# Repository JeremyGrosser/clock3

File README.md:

This repository contains firmware for my 3 time zone clock based on the [Adafruit Feather M0 Wifi](https://www.adafruit.com/product/3010). This project is very incomplete and is unlikely to be reproducible with the code listed here.

Some of the software components (eg. samd21 drivers) may be useful to others, so I'm making this repository public, but have no intention to maintain it long term.

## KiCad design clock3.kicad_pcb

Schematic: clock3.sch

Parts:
BAT1: BS-7; Battery_Holder_Coin_2032_BS-7; MPN BS-7; Digi-Key_PN BS-7-ND
BOOT1, BOOT2: EG1218; Switch_Slide_11.6x4mm_EG1218; MPN EG1218; Digi-Key_PN EG1903-ND
C1, C2, C9: 4.7uF; C_0603_1608Metric
C3: 10uF; C_0805_2012Metric
C4, C5: 16pF; C_0603_1608Metric
C6, C7, C8, C12, C13, C14, C15: 100nF; C_0603_1608Metric
C10: 10nF; C_0603_1608Metric
C11: 1uF; C_0603_1608Metric
C17, C18: 5pF; C_0603_1608Metric
D1, D2, D3, D4: LED; LED_1206_3216Metric
J1: 10118194-0001LF; USB_Micro_B_Female_10118194-0001LF; MPN 10118194-0001LF; Digi-Key_PN 609-4618-1-ND
J2: SWD; Molex_KK-254_AE-6410-06A_1x06_P2.54mm_Vertical
J3, J4, J5: Conn_01x06_Male; Molex_KK-254_AE-6410-06A_1x06_P2.54mm_Vertical
MK1, MK2, MK3, MK4: Mounting_Hole_PAD; MountingHole_2.2mm_M2_DIN965_Pad
R2, R3: 10k; R_0603_1608Metric
R4, R5, R6, R7: R; R_0603_1608Metric
S1, S2, S3, S4: B3F-3150
U1: AP2114H-3_3TRG1; SOT-223; MPN AP2114H-3.3TRG1; Digi-Key_PN AP2114H-3.3TRG1DICT-ND
U2: STM32F102CBTx; LQFP-48_7x7mm_P0.5mm
Y1: 8MHz 18pF 30ppm; Crystal_SMD_HC49-US_AT49
Y2: 32.768kHz 12.5pF 20ppm; Crystal_SMD_SeikoEpson_MC146-4Pin_6.7x1.5mm

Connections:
/BOOT0: R2.2, U2.44 (BOOT0)
/BOOT1: R3.2, U2.20 (PB2)
/BUTTON1: C12.2, S1.1, U2.28 (PB15)
/BUTTON2: C13.2, S2.1, U2.27 (PB14)
/BUTTON3: C14.2, S3.1, U2.26 (PB13)
/I2C1_SCL: J3.4, J4.4, J5.4, U2.42 (PB6)
/I2C1_SDA: J3.3, J4.3, J5.3, U2.43 (PB7)
/LED1: D1.1, U2.10 (PA0)
/LED2: D2.1, U2.11 (PA1)
/LED3: D3.1, U2.29 (PA8)
/SWCLK: J2.2, U2.37 (PA14)
/SWDIO: J2.4, U2.34 (PA13)
/SWO: J2.6, U2.39 (PB3)
/USB_D+: J1.3, U2.33 (PA12)
/USB_D-: J1.2, U2.32 (PA11)
/VBAT: BAT1.Pos, U2.1 (VBAT)
/~RESET: C15.2, J2.5, S4.1, U2.7 (NRST)
GND: BAT1.Neg, BOOT1.3, BOOT2.3, C1.2, C2.2, C3.2, C4.2, C5.2, C6.2, C7.2, C8.2, C9.2, C10.2, C11.2, C12.1, C13.1, C14.1, C15.1, C17.2, C18.2, J1.4, J1.5, J1.SH, J2.3, J3.2, J3.6, J4.2, J4.6, J5.2, J5.6, MK1.1, MK2.1, MK3.1, MK4.1, S1.2, S1.3, S1.4, S2.2, S2.3, S2.4, S3.2, S3.3, S3.4, S4.2, S4.3, S4.4, U1.1, U2.8 (VSSA), U2.23 (VSS), U2.35 (VSS), U2.47 (VSS)
unnamed: BOOT1.2, R2.1
unnamed: BOOT2.2, R3.1
unnamed: C4.1, U2.5 (PD0), Y1.2
unnamed: C5.1, U2.6 (PD1), Y1.1
unnamed: C17.1, U2.3 (PC14), Y2.2
unnamed: C18.1, U2.4 (PC15), Y2.1
unnamed: D1.2, R4.2
unnamed: D2.2, R5.2
unnamed: D3.2, R6.2
unnamed: D4.2, R7.2
VCC: C1.1, J1.1, J3.1, J4.1, J5.1, U1.3
VDD: BOOT1.1, BOOT2.1, C2.1, C3.1, C6.1, C7.1, C8.1, C9.1, C10.1, C11.1, J2.1, J3.5, J4.5, J5.5, R4.1, R5.1, R6.1, R7.1, U1.2, U1.4, U2.9 (VDDA), U2.24 (VDD), U2.36 (VDD), U2.48 (VDD)

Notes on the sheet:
POWER 5V IN 3.3V @ 1A OUT
DEBUG
LED DISPLAYS
USB
BUTTONS AND SWITCHES
WIFI
LEDS
VDD3
VDDA

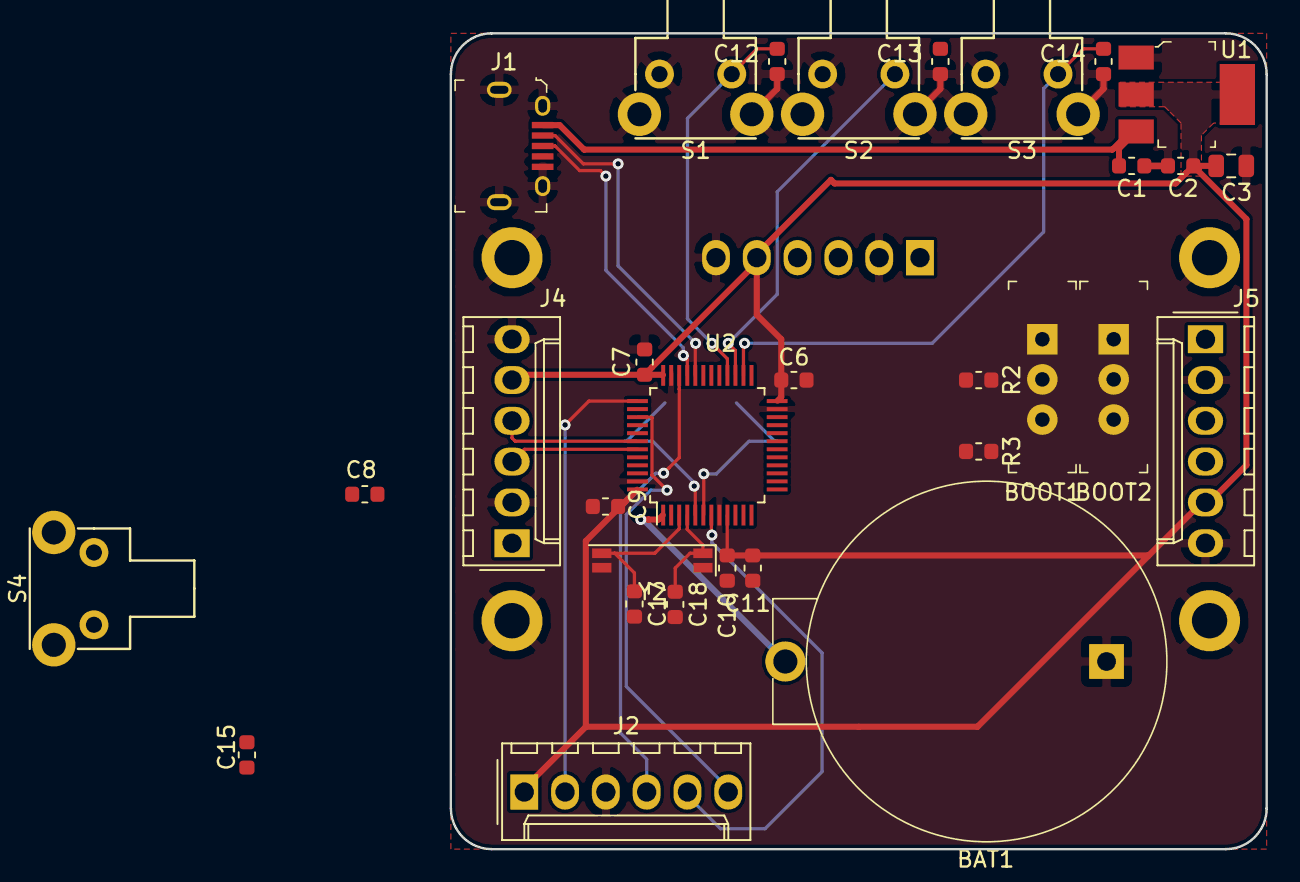
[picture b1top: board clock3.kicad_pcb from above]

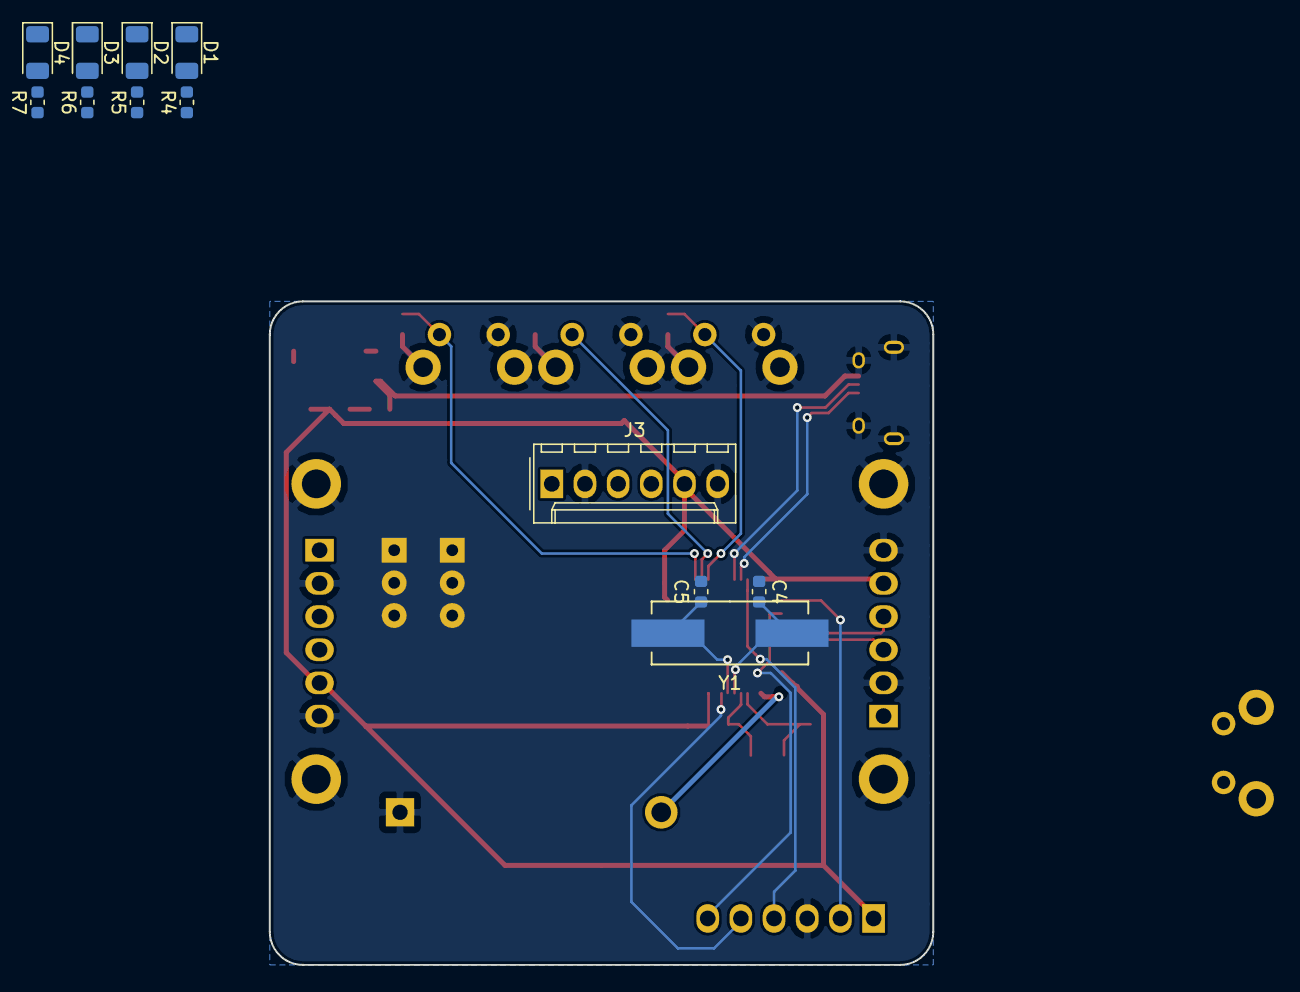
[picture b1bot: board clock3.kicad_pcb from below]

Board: 2 copper layers, 50.8 x 50.8 mm, 47 parts (12 on the bottom side), 30 nets.

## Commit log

2018-07-23 fw/build ignore
2018-07-23 Routing complete
2018-07-24 SAMD21 rewrite
2018-07-24 Refactor into multiple boards, gpio support
2018-07-25 Working blocking uart
2018-07-26 Now with rtc and power saving
2018-07-26 winc1500 driver
2018-07-27 i2c wip
2018-07-28 Loopy LEDs!
2018-07-29 Working clock!
2018-08-02 blinky on ada3010
2018-08-03 Nuke unused driver code
2018-08-03 SPI clocks but no data moves
2018-08-04 Wifi is responding, add EIC
2018-08-04 No interrupts from driver or device
2018-08-05 Integrate I2C display on feather proto
2018-08-05 Refactor EIC into gpio
2018-08-05 Add needed winc driver code
2018-08-05 Move driver headers into driver dirs
2018-08-05 ht16k33 dimming, disable atw driver, disable lto
2018-08-07 Less uart, more speed
2018-09-30 Add another segment display, openocd config for ada3010
2018-09-30 Pull in atw driver
2018-10-10 Clean slate for hardware
2021-01-23 ht16k33 init
2021-01-24 seven segment
2021-01-25 esp8266
2021-01-26 works kinda
2021-10-14 Add README
2021-10-14 LICENSE
2021-10-14 Add a link to the feather board in README
